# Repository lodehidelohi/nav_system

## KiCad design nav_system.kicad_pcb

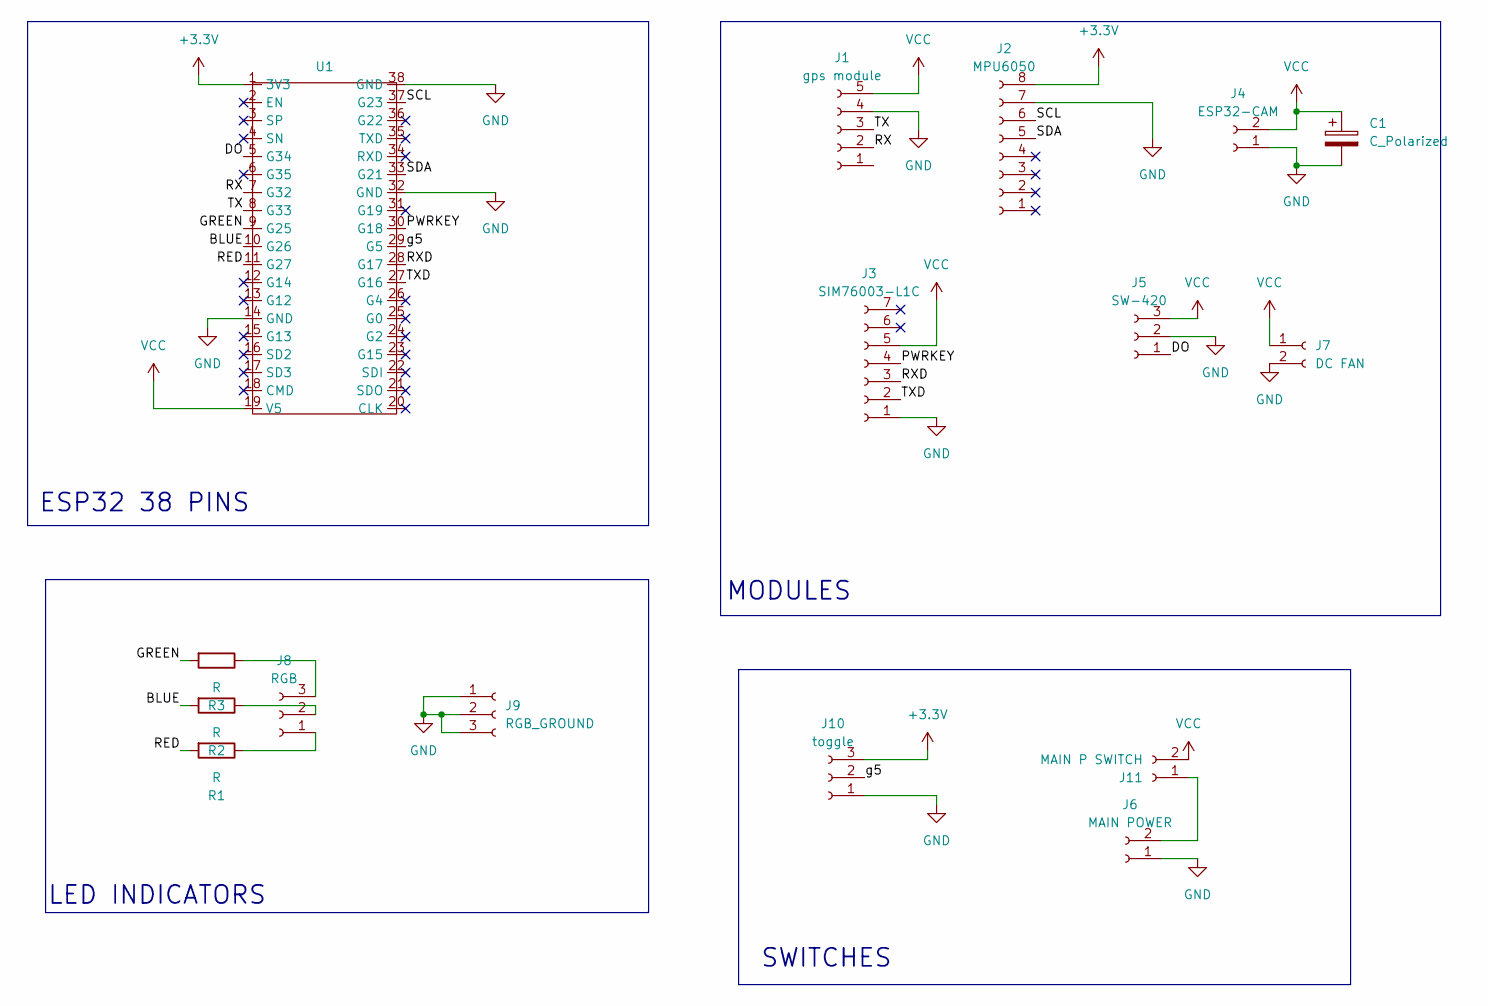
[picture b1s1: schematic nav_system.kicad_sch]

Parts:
C1: C_Polarized; CP_Radial_D10.0mm_P3.50mm
J1: gps module; PinHeader_1x05_P2.54mm_Vertical
J2: MPU6050; PinSocket_1x08_P2.54mm_Vertical
J3: SIM76003-L1C; PinSocket_1x07_P2.54mm_Vertical
J4: ESP32-CAM; JST_XH_B2B-XH-A_1x02_P2.50mm_Vertical
J5: SW-420; PinSocket_1x03_P2.54mm_Vertical
J6: MAIN POWER; JST_XH_B2B-XH-A_1x02_P2.50mm_Vertical
J7: DC FAN; JST_XH_B2B-XH-A_1x02_P2.50mm_Vertical
J8: RGB; JST_XH_B3B-XH-A_1x03_P2.50mm_Vertical
J9: RGB_GROUND; JST_XH_B3B-XH-A_1x03_P2.50mm_Vertical
J10: toggle; JST_XH_B3B-XH-A_1x03_P2.50mm_Vertical
J11: MAIN P SWITCH; JST_XH_B2B-XH-A_1x02_P2.50mm_Vertical
R1, R2, R3: R; R_Axial_DIN0204_L3.6mm_D1.6mm_P5.08mm_Horizontal
U1: ESP32_38

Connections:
+3.3V: J2.8, J10.3, U1.1 (3V3)
/BLUE: R2.2, U1.10 (G26)
/DO: J5.1, U1.5 (G34)
/GREEN: R3.2, U1.9 (G25)
/PWRKEY: J3.4, U1.30 (G18)
/RED: R1.2, U1.11 (G27)
/RX: J1.2, U1.7 (G32)
/RXD: J3.3, U1.28 (G17)
/SCL: J2.6, U1.37 (G23)
/SDA: J2.5, U1.33 (G21)
/TX: J1.3, U1.8 (G33)
/TXD: J3.2, U1.27 (G16)
/g5: J10.2, U1.29 (G5)
GND: C1.2, J1.4, J2.7, J3.1, J4.1, J5.2, J6.1, J7.2, J9.1, J9.2, J9.3, J10.1, U1.14 (GND), U1.32 (GND), U1.38 (GND)
unnamed: J8.1, R1.1
unnamed: J8.2, R2.1
unnamed: J8.3, R3.1
unnamed: J6.2, J11.1
VCC: C1.1, J1.5, J3.5, J4.2, J5.3, J7.1, J11.2, U1.19 (V5)

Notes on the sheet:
MODULES
LED INDICATORS
SWITCHES
ESP32 38 PINS

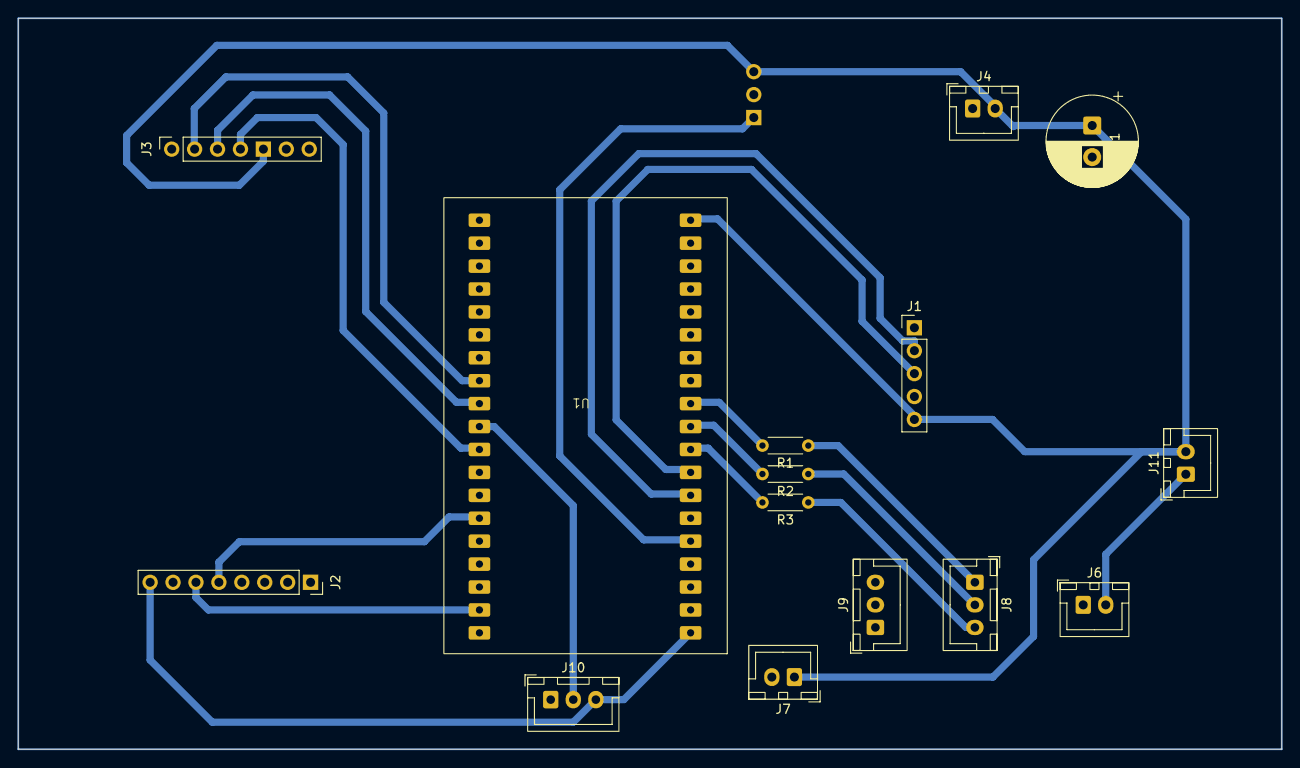
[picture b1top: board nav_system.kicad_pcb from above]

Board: 2 copper layers, 140.0 x 81.0 mm, 16 parts (1 on the bottom side), 19 nets.

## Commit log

2026-04-30 Initial comit
2026-04-30 Ignore .history folder
2026-05-01 Trying to add 3d model
2026-05-01 setup
2026-05-04 Nav_system.2.0
2026-05-05 modify plot files
2026-05-06 update symbols
